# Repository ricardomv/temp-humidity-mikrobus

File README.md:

# temp-humidity-mikrobus
MikroBus sensor board for temperature and humidity.

Tested with:
 - [Microchip Explorer 16/32 Dev Kit](https://www.microchip.com/DevelopmentTools/ProductDetails/DM240001-2) using PIC24FJ1024GB610
 - Raspberry Pi 3 with [Pi 3 click shield](https://www.mikroe.com/pi-3-click-shield)
 
## Build

Raspberry Pi:

Install bcm2835 linux library

`cd raspberry; make`

Microchip Explorer 16/32:

 - Open MPLabX IDE
 - Open project `temp-humid.X`
 - Press Build

## Components

 - [MCP3201 - 12-Bit A/D Converter with SPI™](https://www.microchip.com/wwwproducts/en/MCP3201)
 - [HIH-5030 - Humidity Sensor](https://sensing.honeywell.com/sensors/humidity-sensors/HIH-5030-5031-series)
 - [AD592 - Current Output – Precision IC Temperature Transducer](https://www.analog.com/en/products/ad592.html)
 - [MCP1501 - Voltage reference](https://www.microchip.com/wwwproducts/en/MCP1501)
 - [1040310 - microSD Memory Card Connector](https://www.molex.com/molex/products/datasheet.jsp?part=active/1040310811_MEMORY_CARD_SOCKET.xml&channel=Products&Lang=en-US)

## PCB (compatible with mikroBUS™)

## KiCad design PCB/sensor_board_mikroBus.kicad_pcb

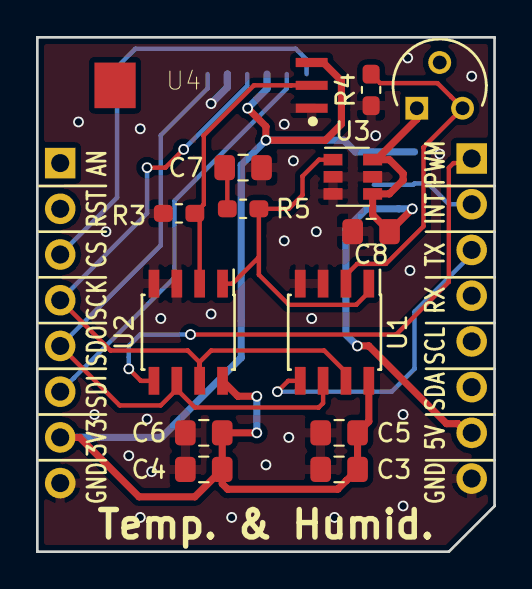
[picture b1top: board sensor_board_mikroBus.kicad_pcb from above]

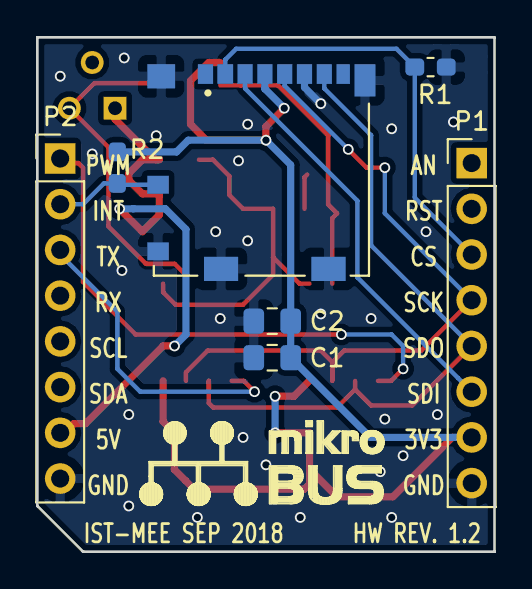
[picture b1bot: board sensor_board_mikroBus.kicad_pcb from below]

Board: 2 copper layers, 25.4 x 28.6 mm, 21 parts (7 on the bottom side), 14 nets.

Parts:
C1, C3, C4: 10uF; C_0805_2012Metric_Pad1.15x1.40mm_HandSolder
C2: 100nF; C_0805_2012Metric_Pad1.15x1.40mm_HandSolder
C5, C6: 1uF; C_0805_2012Metric_Pad1.15x1.40mm_HandSolder
C7, C8: 2.2uF; C_0805_2012Metric_Pad1.15x1.40mm_HandSolder
J1: Molex_0475710001; MOLEX_104031-0811
P1, P2: HEADER_M_2.54MM_1R8P_ST_AU_PTH; PinHeader_1x08_P2.54mm_Vertical
R1, R2: 100k; R_0603_1608Metric_Pad1.05x0.95mm_HandSolder
R3: 65k; R_0603_1608Metric_Pad1.05x0.95mm_HandSolder
R4: 2k; R_0603_1608Metric_Pad1.05x0.95mm_HandSolder
R5: 50R; R_0603_1608Metric_Pad1.05x0.95mm_HandSolder
U1, U2: MCP3201; SOIC-8_3.9x4.9mm_P1.27mm
U3: MCP1501-SOT-23; SOT-23-6
U4: HIH-5030-001; HONEYWELL_HIH-5030-001
U5: AD592BN; TO127P520X660-3P

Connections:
+3.3V: C1.1, C2.1, C3.1, C4.1, C5.1, C6.1, J1.4, P1.7, R2.2, U1.8, U2.8, U4.3
+5V: C8.1, P2.7, U3.4, U3.6, U5.1
CS: J1.2, P1.3, R1.1
GND: C1.2, C2.2, C3.2, C4.2, C5.2, C6.2, C7.2, C8.2, J1.6, J1.10, J1.G1, J1.G2, J1.G3, J1.G4, P1.8, P2.8, R1.2, R3.1, R4.1, U1.3, U1.4, U2.3, U2.4, U3.2, U3.3, U3.5, U4.1
INT: J1.9, P2.2, R2.1
MISO: J1.7, P1.5, U1.6, U2.6
MOSI: J1.3, P1.6
unnamed: C7.1, R5.1
PWM: P2.1, U2.5
SCK: J1.5, P1.4, U1.7, U2.7
TX: P2.3, U1.5
V_in_humid: R3.2, U2.2, U4.2
V_in_temp: R4.2, U1.2, U5.3
Vref: R5.2, U1.1, U2.1, U3.1

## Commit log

2018-11-18 Working uSD card and ADC
2018-11-18 Use timer to blink led.
2018-11-18 Move peripheral configurations to function
2018-11-18 Use timer3 for data acquisition
2018-11-19 Add uart peripheral
2018-11-20 Cleanup main.c
2018-11-20 Use correct namespace in fat16 libs
2018-11-20 Add function LCD_PutLongInt to LCD driver
2018-11-20 Add rtcc peripheral
2018-11-20 Add one more ADC to aquire Temperature and humidity simultaneosly
2018-11-20 Lower sample count for now
2018-11-26 Set CS pins for Temp an Humid ADCs
2018-11-28 Make propper sensor values calculation
2018-11-29 Improve debug messages
2018-11-29 Update configuration file
2018-11-29 Change to DCO at 30MHz
2018-11-29 Display sdcard statistics in LCD and UART
2018-12-01 Add PCB schematic and layout
2018-12-02 Add alarm code to RTC peripheral Currently only blinks led D4 every second 24 times This will be used to change files dutring aquisition
2018-12-02 Remove magic number
2018-12-02 Change clock frequency in ADC SPI comunication
2018-12-02 Make rtcc compatible with posix time.h Years start in 1900 Months are counted since January ranging from 0-11
2018-12-02 Cleanup RTCC configuration
2018-12-02 Display time in LCD
2018-12-02 Cleanup OSC config and move pragma configs to mcu.c
2018-12-02 Cleanup code that changes SPI baudrate
2018-12-03 LCD: Display human readable size of data written to sdcard
2018-12-03 End data aquisition after a defined time. After 1 minute data aquisition ends.
2018-12-03 Change CS pin for the temperature ADC
2018-12-03 Change temperature variable type to float
2018-12-03 Fix missing option in RTCC_REPEAT enum
2018-12-05 PCB: Change sdcard pin connected to ground.
2018-12-05 PCB: Update revision
2018-12-06 Add development board components
2018-12-09 Fix calculations for ADC voltage
2018-12-09 Use also button S3 to stop data aquisition
2018-12-09 Fix uart_read_noblock to return number of bytes read from uart
2018-12-09 Sync rtcc time from UART
2018-12-09 Count seconds until end of data aquisiton with rtcc interrupt
2018-12-09 Add miliseconds counter to data
2018-12-09 Print error messages only one time
2018-12-12 PCB: Fix noise generated by sensor in Vref
2018-12-13 utils: Port prgram to set RTC time to python
2018-12-14 Start aquisition even if SD card is not present
2018-12-20 PCB: Add schematic subtitle
2018-12-20 Change interface using the buttons and LCD
2018-12-21 Move MPLABX project to own folder
2018-12-23 Add Raspberry Pi 2B/3B code to read sensor values
2019-01-03 Add README.md file
2019-01-03 Add components section to readme.md
